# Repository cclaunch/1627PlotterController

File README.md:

Attaching a 1627 Plotter to an IBM 1130 system required the installation of an IBM double width SLT card 5806223 into
gate A-C1 in slots M4/M5. The 1627 was an IBM badged version of the Calcomp 565 or 563 plotters.

This project provides a functional equivalent to that IBM SLT card that can be plugged into the IBM 1130 to add 
the controller logic so that software can command plotter movements and see its status in the same way as
the IBM card. PCBWay.com sponsored production of the main printed circuit board 
during development of this project. The results were excellent.

A connector is built to plug into the 1130 card compartment to wire the plotter into the system, 
in conjunction with an SMS power paddle card to plug into the SMS power connector block.

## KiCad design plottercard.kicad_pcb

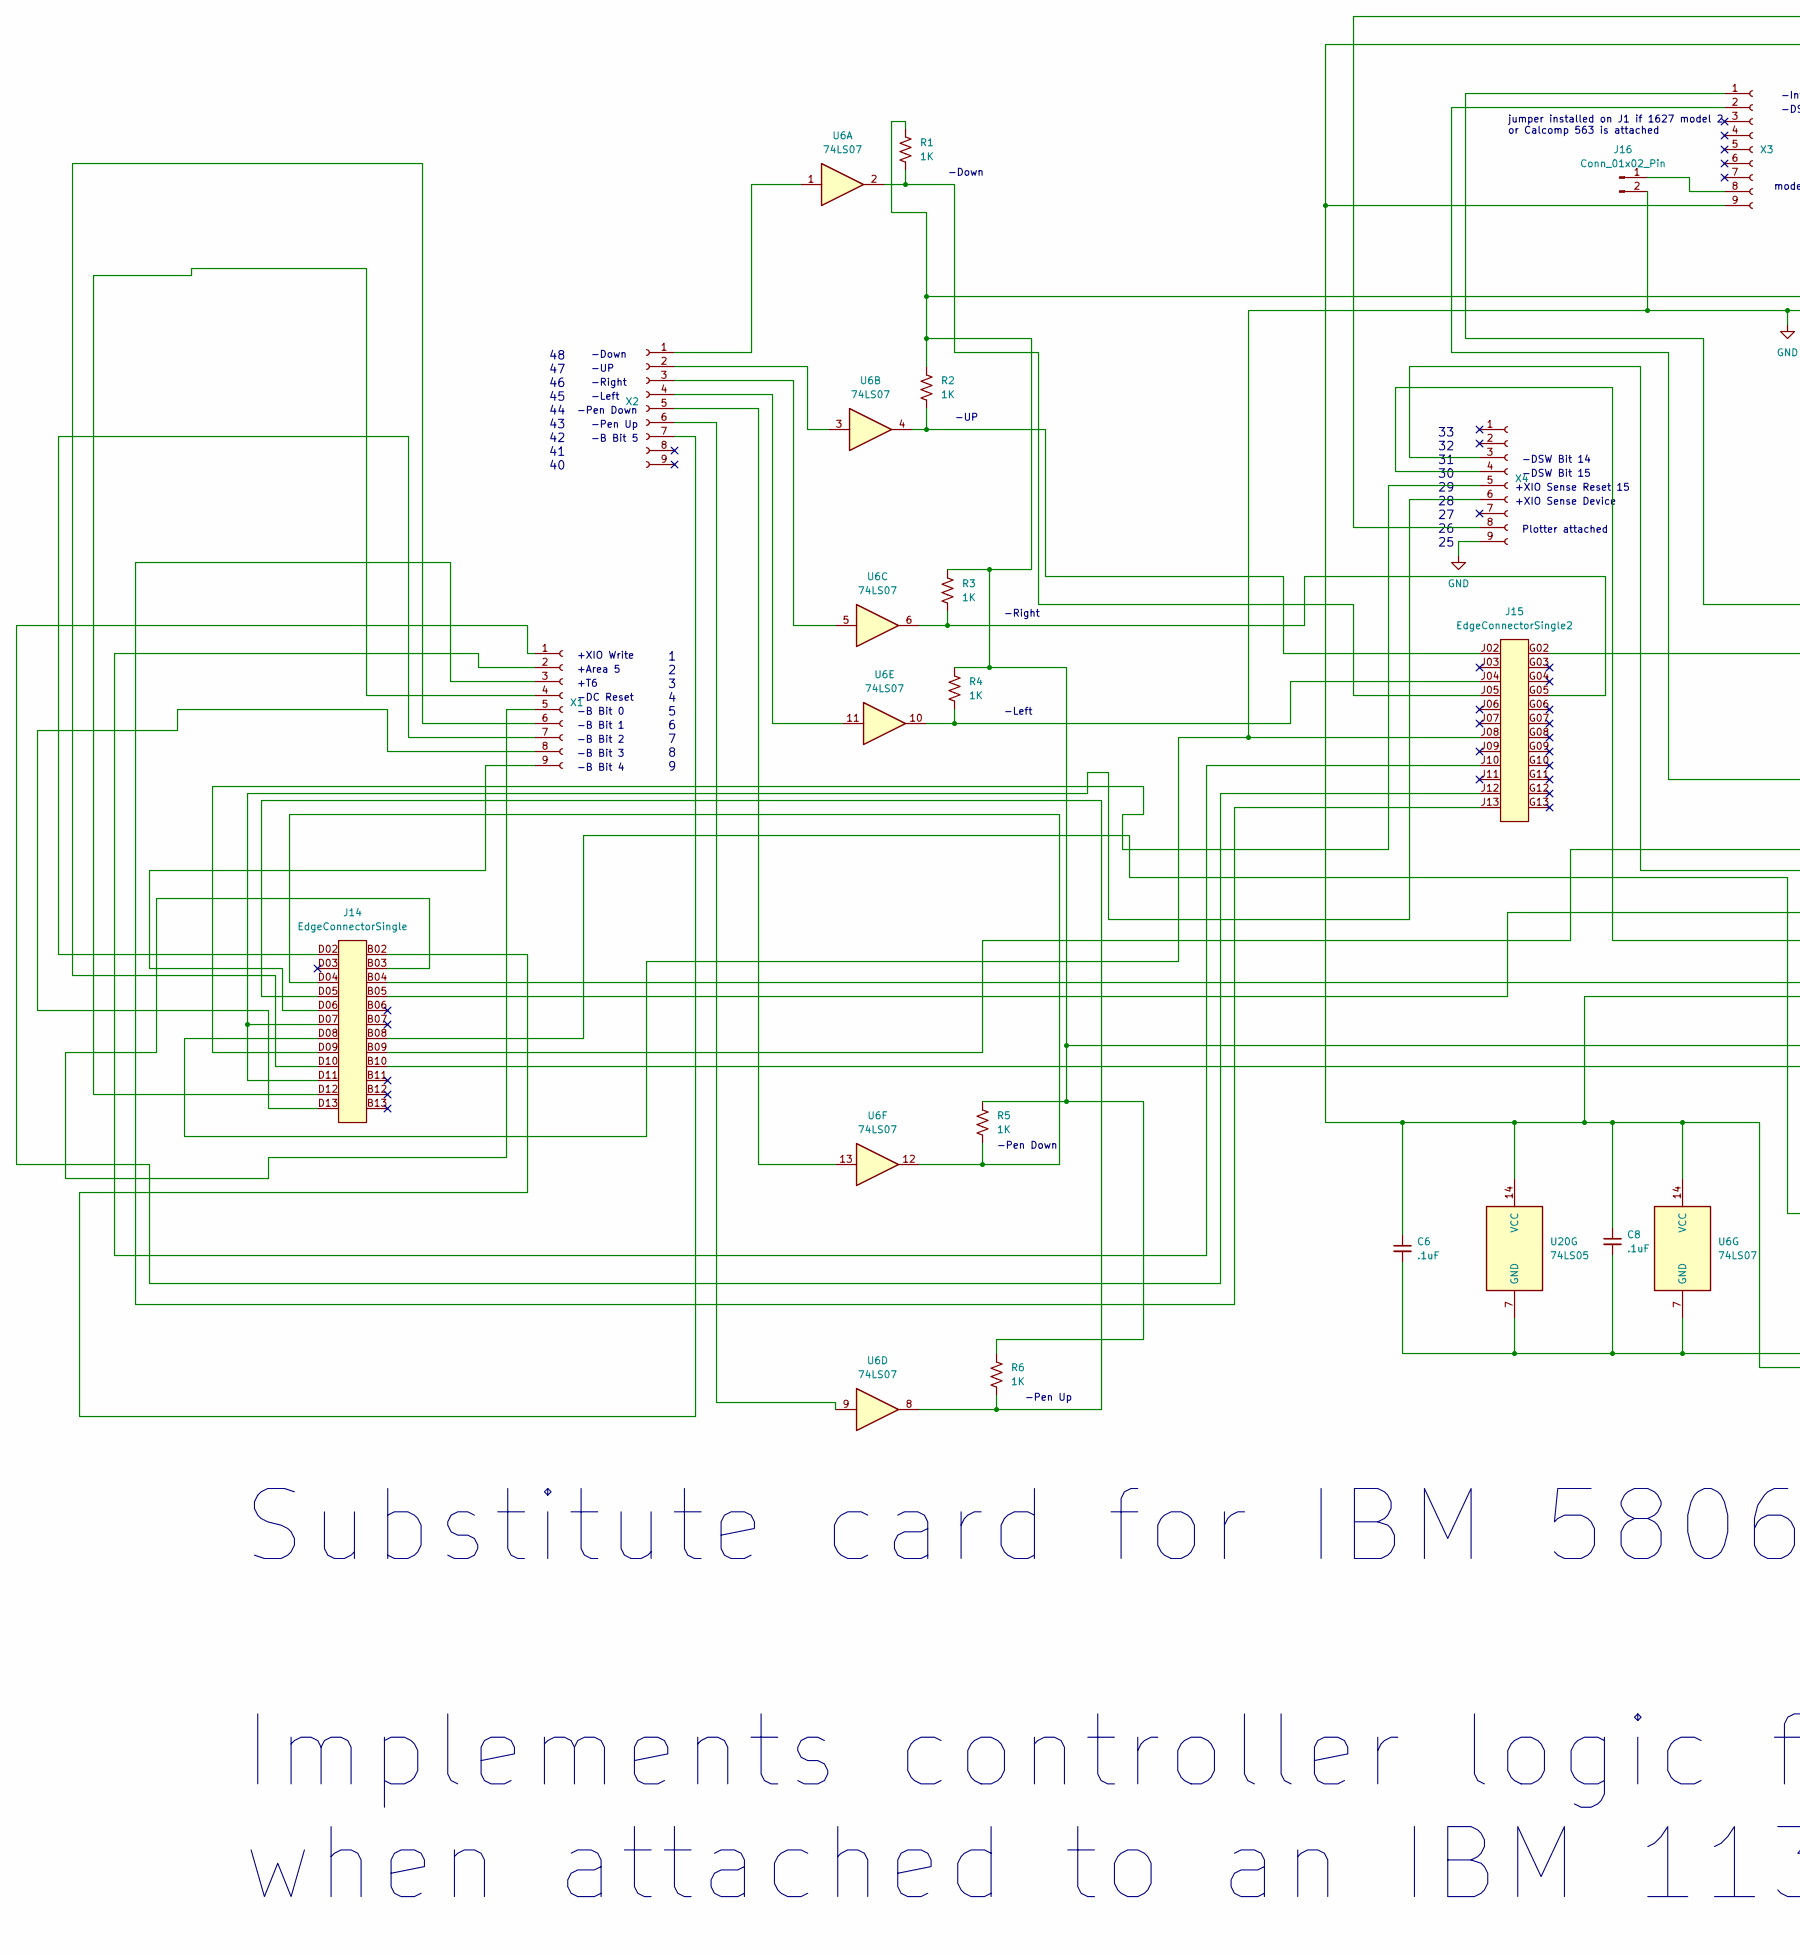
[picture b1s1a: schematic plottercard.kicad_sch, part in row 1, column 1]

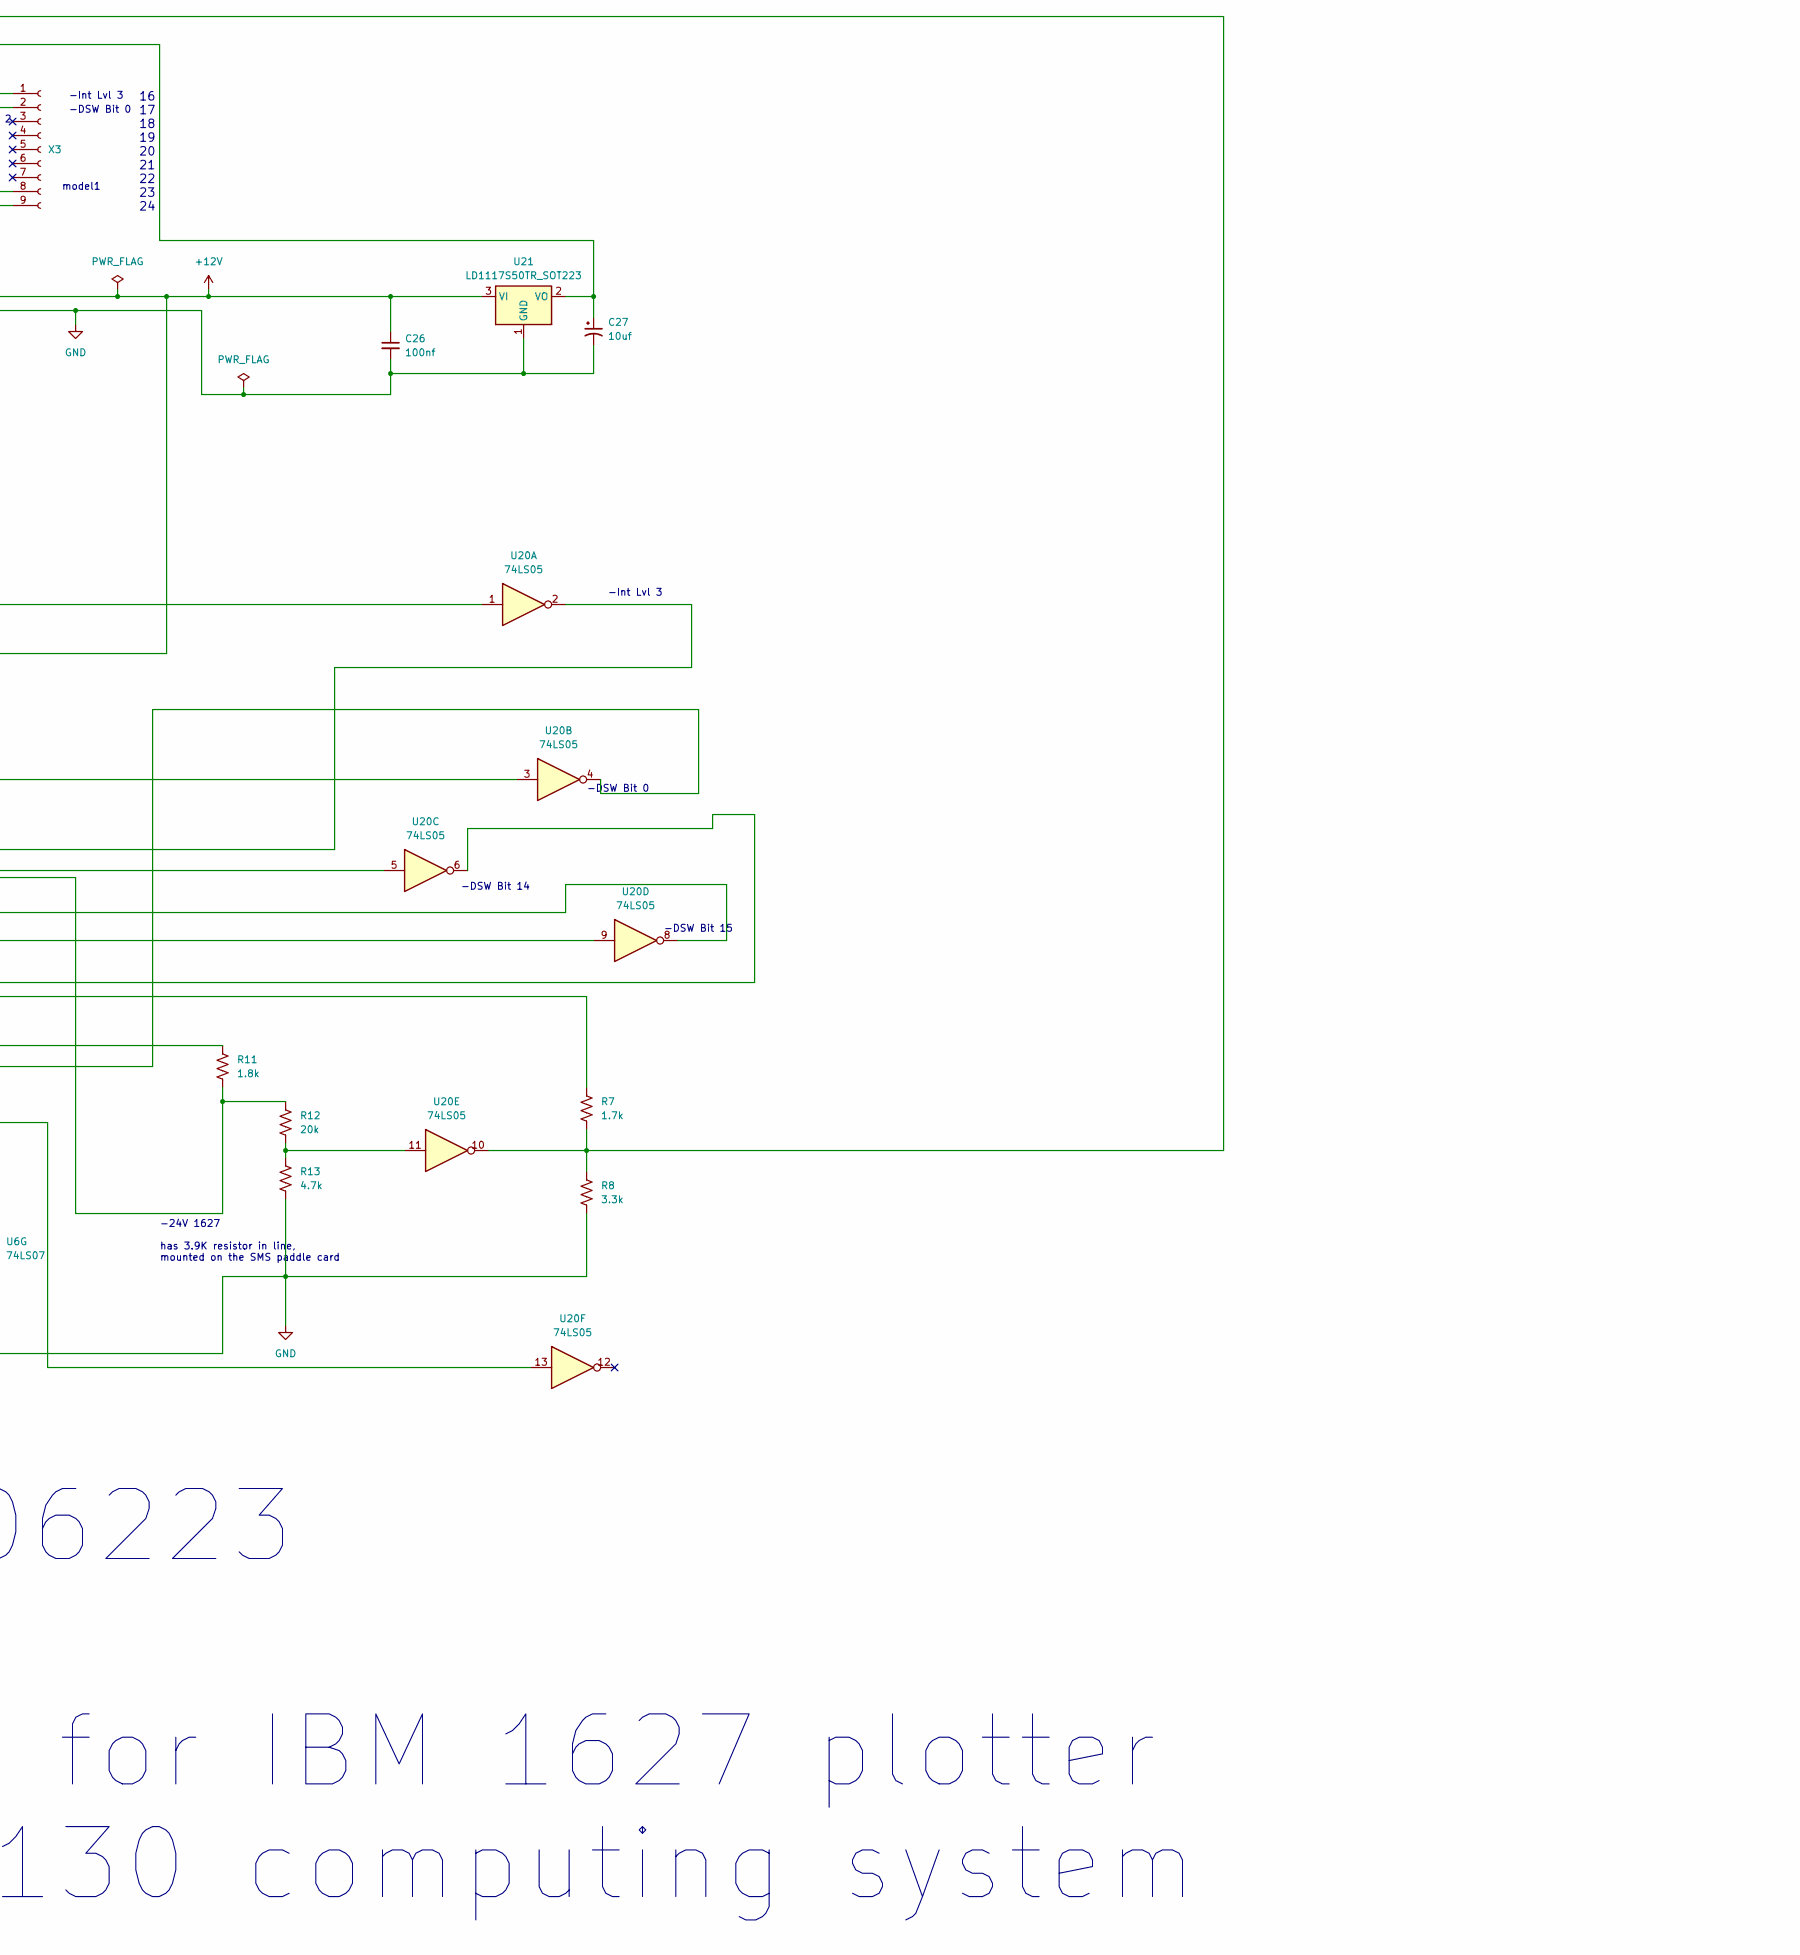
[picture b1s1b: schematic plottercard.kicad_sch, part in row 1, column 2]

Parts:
C6, C8: .1uF; C_0805_2012Metric
C26: 100nf; C_0805_2012Metric
C27: 10uf; C_0805_2012Metric
J14: EdgeConnectorSingle; PlugConnector
J15: EdgeConnectorSingle2; PlugConnector2
J16: Conn_01x02_Pin; PinHeader_1x02_P2.54mm_Vertical
R1, R2, R3, R4, R5, R6: 1K; R_0805_2012Metric
R7: 1.7k; R_0805_2012Metric
R8: 3.3k; R_0805_2012Metric
R11: 1.8k; R_0805_2012Metric
R12: 20k; R_0805_2012Metric
R13: 4.7k; R_0805_2012Metric
U6: 74LS07; SOIC-14_3.9x8.7mm_P1.27mm
U20: 74LS05; SOIC-14_3.9x8.7mm_P1.27mm
U21: LD1117S50TR_SOT223; SOT-223-3_TabPin2
X1, X2, X3, X4: Conn_01x09_Socket; PinSocket_1x09_P2.54mm_Vertical

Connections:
+12V: C26.1, J15.G02, R1.1, R2.1, R3.1, R4.1, R5.1, R6.1, R11.1, U21.3 (VI)
GND: C6.2, C8.2, C26.2, C27.2, J14.D08, J15.J08, J16.2, R8.2, R13.2, U6.7 (GND), U20.7 (GND), U21.1 (GND), X4.9
unnamed: J14.B04, U20.6
unnamed: J14.B05, U20.8
unnamed: J14.B08, R11.2, R12.1
unnamed: J14.B09, U20.2
unnamed: J14.B10, U20.4
unnamed: J14.D04, R5.2, U6.12
unnamed: J14.D05, R6.2, U6.8
unnamed: J15.G05, R3.2, U6.6
unnamed: J15.J02, R2.2, U6.4
unnamed: J15.J04, R4.2, U6.10
unnamed: J15.J05, R1.2, U6.2
unnamed: J16.1, X3.8
unnamed: R12.2, R13.1, U20.11
unnamed: C6.1, C8.1, C27.1, R7.1, U6.14 (VCC), U20.13, U20.14 (VCC), U21.2 (VO), X3.9
unnamed: J15.J12, X1.1
unnamed: J15.J10, X1.2
unnamed: J15.J13, X1.3
unnamed: J14.D12, X1.4
unnamed: J14.B03, X1.5
unnamed: J14.D10, X1.6
unnamed: J14.D02, X1.7
unnamed: J14.D13, X1.8
unnamed: J14.D06, X1.9
unnamed: U6.1, X2.1
unnamed: U6.3, X2.2
unnamed: U6.5, X2.3
unnamed: U6.11, X2.4
unnamed: U6.13, X2.5
unnamed: U6.9, X2.6
unnamed: J14.B02, X2.7
unnamed: U20.1, X3.1
unnamed: U20.3, X3.2
unnamed: U20.5, X4.3
unnamed: U20.9, X4.4
unnamed: J14.D09, X4.5
unnamed: J14.D07, J14.D11, X4.6
unnamed: R7.2, R8.1, U20.10, X4.8

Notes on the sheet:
-B Bit 2
jumper installed on J1 if 1627 model 2 or Calcomp 563 is attached
-Down
-B Bit 3
-UP
Substitute card for IBM 5806223 Implements controller logic for IBM 1627 plotter when attached to an IBM 1130 computing system
-DSW Bit 15
16 17 18 19 20 21 22 23 24
-B Bit 1
-Pen Up
-Right
1 2 3 4 5 6 7 8 9
-Pen Down
+XIO Sense Reset 15
Plotter attached
-DSW Bit 0
-DSW Bit 14
48 47 46 45 44 43 42 41 40
-Left
-24V 1627 has 3.9K resistor in line, mounted on the SMS paddle card
model1
+Area 5
33 32 31 30 29 28 27 26 25
+T6
-Int Lvl 3
+XIO Write
-DC Reset
-B Bit 4
-B Bit 0
+XIO Sense Device
-B Bit 5

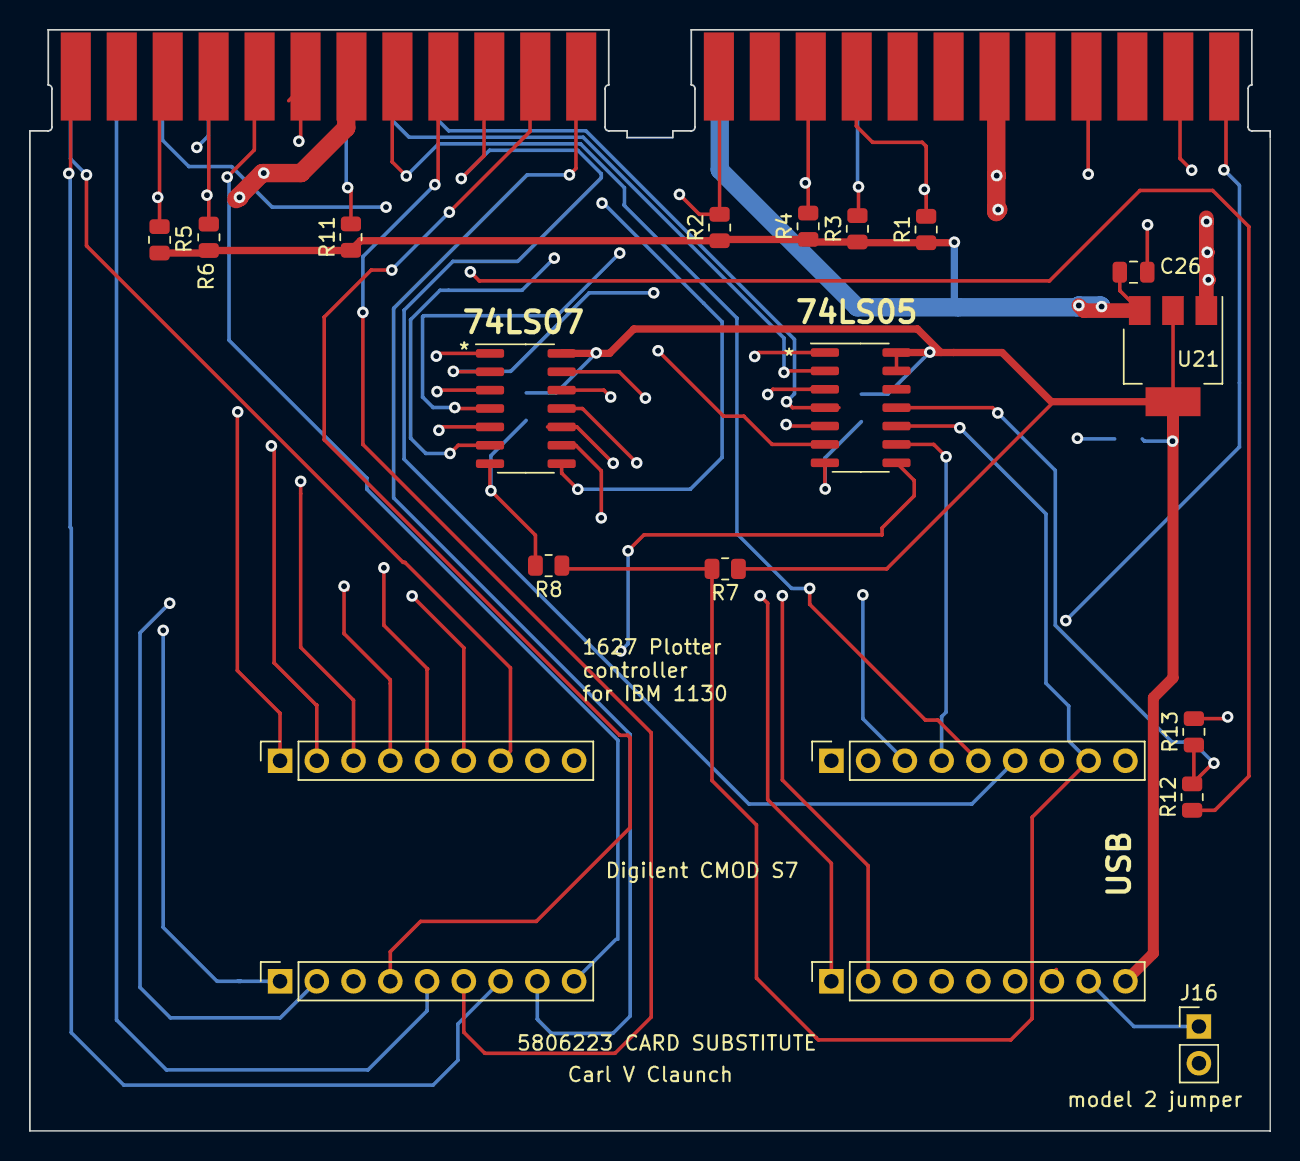
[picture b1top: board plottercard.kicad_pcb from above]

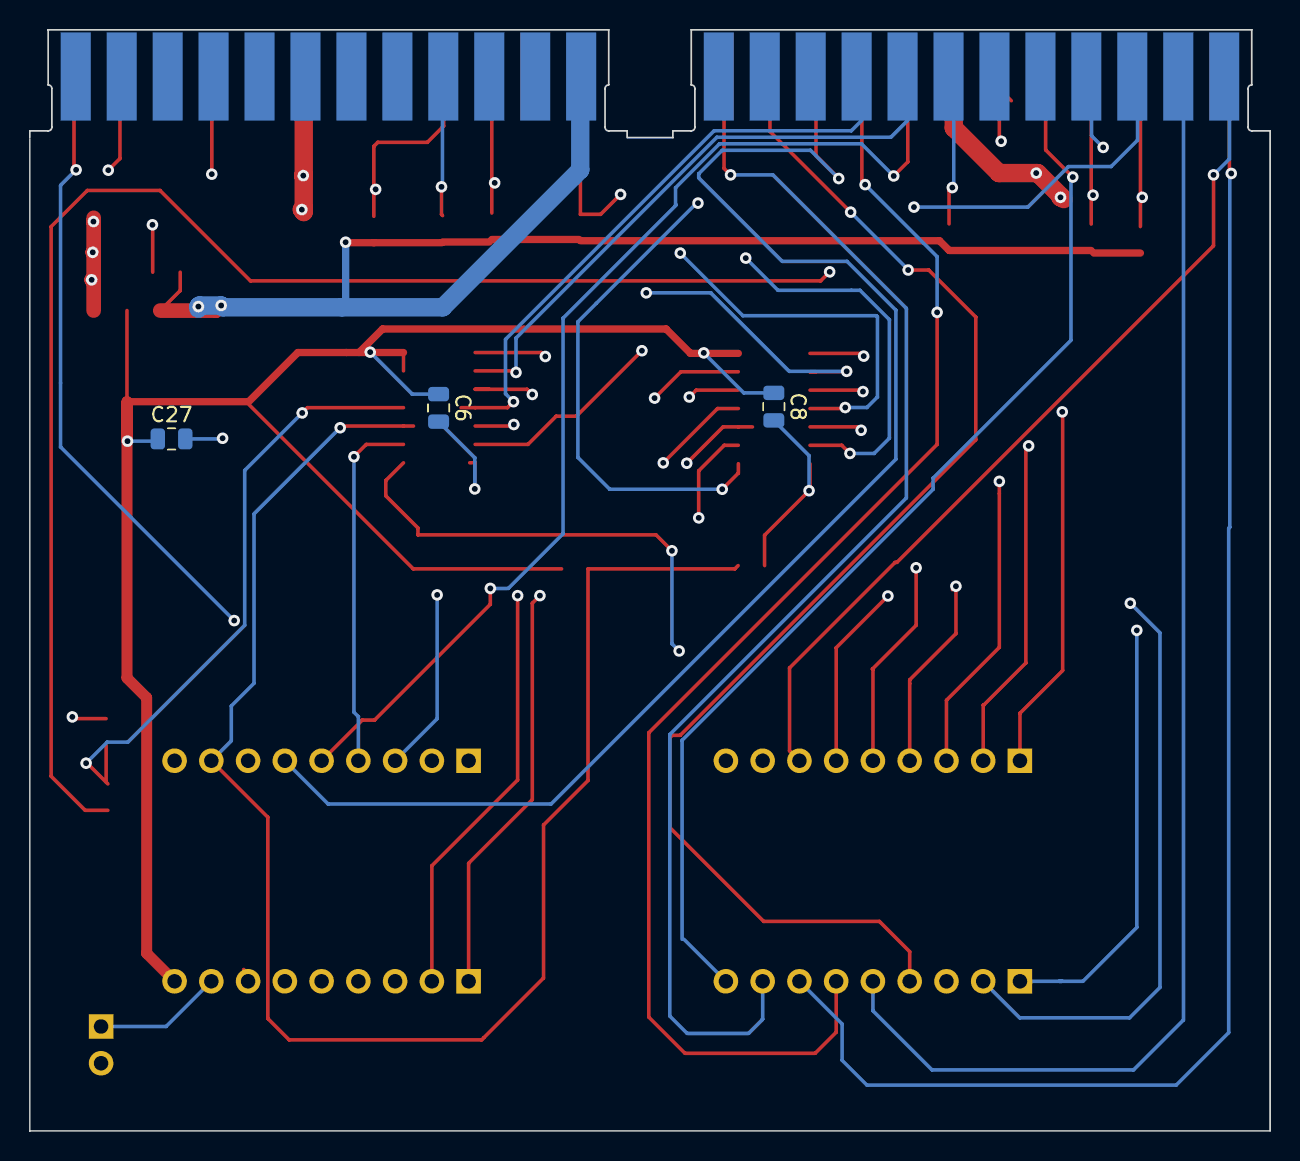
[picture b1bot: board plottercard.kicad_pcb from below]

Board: 4 copper layers, 85.7 x 76.1 mm, 25 parts (3 on the bottom side), 39 nets.

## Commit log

2026-03-19 Initial upload
2026-03-22 Filling out initial repository prior to testing
2026-03-22 Additional file
2026-05-09 After successful bench testing of the card functionality
    Includes simulation test code and code for an Arduino that drives test signals into the card on the bench.
    updated fill of materials
    verilog and configuration file for the CMOD S7 board
2026-05-09 PCB gerber and drill files
2026-05-09 adding PCB files for SMS power card
    Gerber and drill files to build an SMS power card
2026-05-09 adding PCB files for SMS signal paddle card
    gerber and drill files to create SMS paddle card
2026-05-10 update descriptions of plotter bench test driver code
2026-05-10 Describe method of bench testing
    Setup to bench test using Arduino Uno to drive inputs, scope to observe outputs, plus several power supplies, pullup resistors. buffer chips and connections
2026-05-10 Delete 1130 MRAM core replacement theory of operations.pdf
    incorrectly named file. Uploaded version under correct name
2026-05-10 Replaced file under proper name
    Was misnamed on initial upload
2026-05-10 Initial upload
    Describes how to assemble the controller card as well as various cables and connectors.
    Also covers how to test the card.
2026-05-10 Configuration memory file to load CMOD S7 board
    This file can be loaded onto the Digilent CMOD S7 board if it uses the MX25L3233F memory device. Plug the USB cable into the CMOD and into the machine running Vivado. Open the hardware, autoconnect t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
2026-05-11 Improved build and install manual
    Added more details, pictures and cleaned up the writing
2026-05-11 Updated FPGA logic after testing in IBM 1130 system
    This logic works exactly as the original IBM card does, producing the same behaviors, waveforms, timings and voltage levels.
2026-05-11 Updated after successful testing in an IBM 1130
    Minor tweak to two signals
2026-05-11 Up to date KiCad design files
    matching the gerbers and drill files
2026-05-13 Files needed to build Vivado project to create the FPGA code
    A description of the parameters to generate the two bits of IP (clock and FIFO) used in the project, a description of the two constants updated in the Digilent provided serial port module, plus the c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
2026-05-13 Images of the SMS signal and SMS power paddle cards
    What the PCBs will look like if built using the included gerber/drill files
2026-05-13 Update README.md
    minor tweak to description
2026-05-13 Continued refinement of manual
    Added more pictures of key parts and processes. Improved descriptions. Cleaned up text. Optimized to lower size of PDF.
2026-05-13 Acknowledge sponsorship of PCB development
    PCBWay.com covered the costs of building and shipping the main printed circuit card for this project in exchange for mention in my blog covering the project - https://rescue1130.blogspot.com/
2026-05-14 Continued improvement of build/install instructions
    added more pictures, cleaned up text
2026-05-16 Minor edits to document
    Added warning to put power SMS paddle card only in slot PP6
2026-05-22 Update README.md
    edited to add the unicode characters for cents ¢ and logical not ¬
2026-05-22 replace with correct README.md
    prior update inadvertently applied a change from another project to this project's readme file. put back to its correct content.
2026-05-25 Update README.md
    add in mention of sponsor for the PCBs I designed for this project
